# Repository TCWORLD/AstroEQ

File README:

Last Updated: 12/02/2017

Version 7 includes a change to the microstepping mode being used. AstroEQ now has a user selectable stepping modes allowing used of all modes supported by the DRV8825 and A4988 chips. If you have legacy hardware, please read the "Upgrading from 6.x to 7.x firmware" file. The Arduino Mega variant of the design has been adjusted as described in the upgrade file to bring it up to date and as such, it is no longer considered legacy hardware.

A small number of AstroEQ controllers are available to purchase. These can be bought from me on my website (http://www.astroeq.co.uk).

If you have any questions or need support, I have opened an AstroEQ Forum which can be found at http://www.astroeq.co.uk/forum/

The AstroEQ Firmware is currently proving to be very stable. If you do happen across any glitches, let me know as I can usually fix them fairly quickly.

There are two hardware options. Firstly to use an Arduino Mega (Uno is not supported), which requires only two DRV8825 or A4988 driver boards and a couple of capacitors to build.
The second option which is used for purchased controllers is a completely custom hardware which is based around an Atmega162 chip. Although this is not officially supported by the Arduino IDE, I have modified the bootloader to suit.
Schematic and PCB Layout designs are available in this repo for the second option. For the Mega, refer to the PinAssignments.h file for the digital pin numbers to connect the driver boards.

-------------------------------------------------------------------------------------

AstroEQ Arduino code, and Hardware schematics.

AstroEQ was written and designed by Thomas Carpenter.
With thanks Chris over at the EQMOD Yahoo group for help communicating with EQMOD.

AstroEQ is an alternative to the expensive SynScan upgrade. The project acts as a gateway to connect the EQMOD Software (and hence ASCOM planetariums) to a motorised Equatorial mount that lacks Goto functionality.

The EQMOD Project can be found at: http://eq-mod.sourceforge.net/

  Works with EQ3, EQ5, HEQ5, and EQ6 mounts. Along With custom mounts.
 
  Current Config Utility Version: 3.6
  Current Software Verison: 7.5
  Current Hardware Version: 4.6

---------------------------------------------------------------------------------------

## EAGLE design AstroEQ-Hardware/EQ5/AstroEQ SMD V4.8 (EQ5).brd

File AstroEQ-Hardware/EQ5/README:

This is an experimental design I am using for my mount.

It is designed to fit within the shell of a Skywatcher EQ5, though takes a bit of work to install it.

I don't recommend using this design. It is provided as-is without any support.

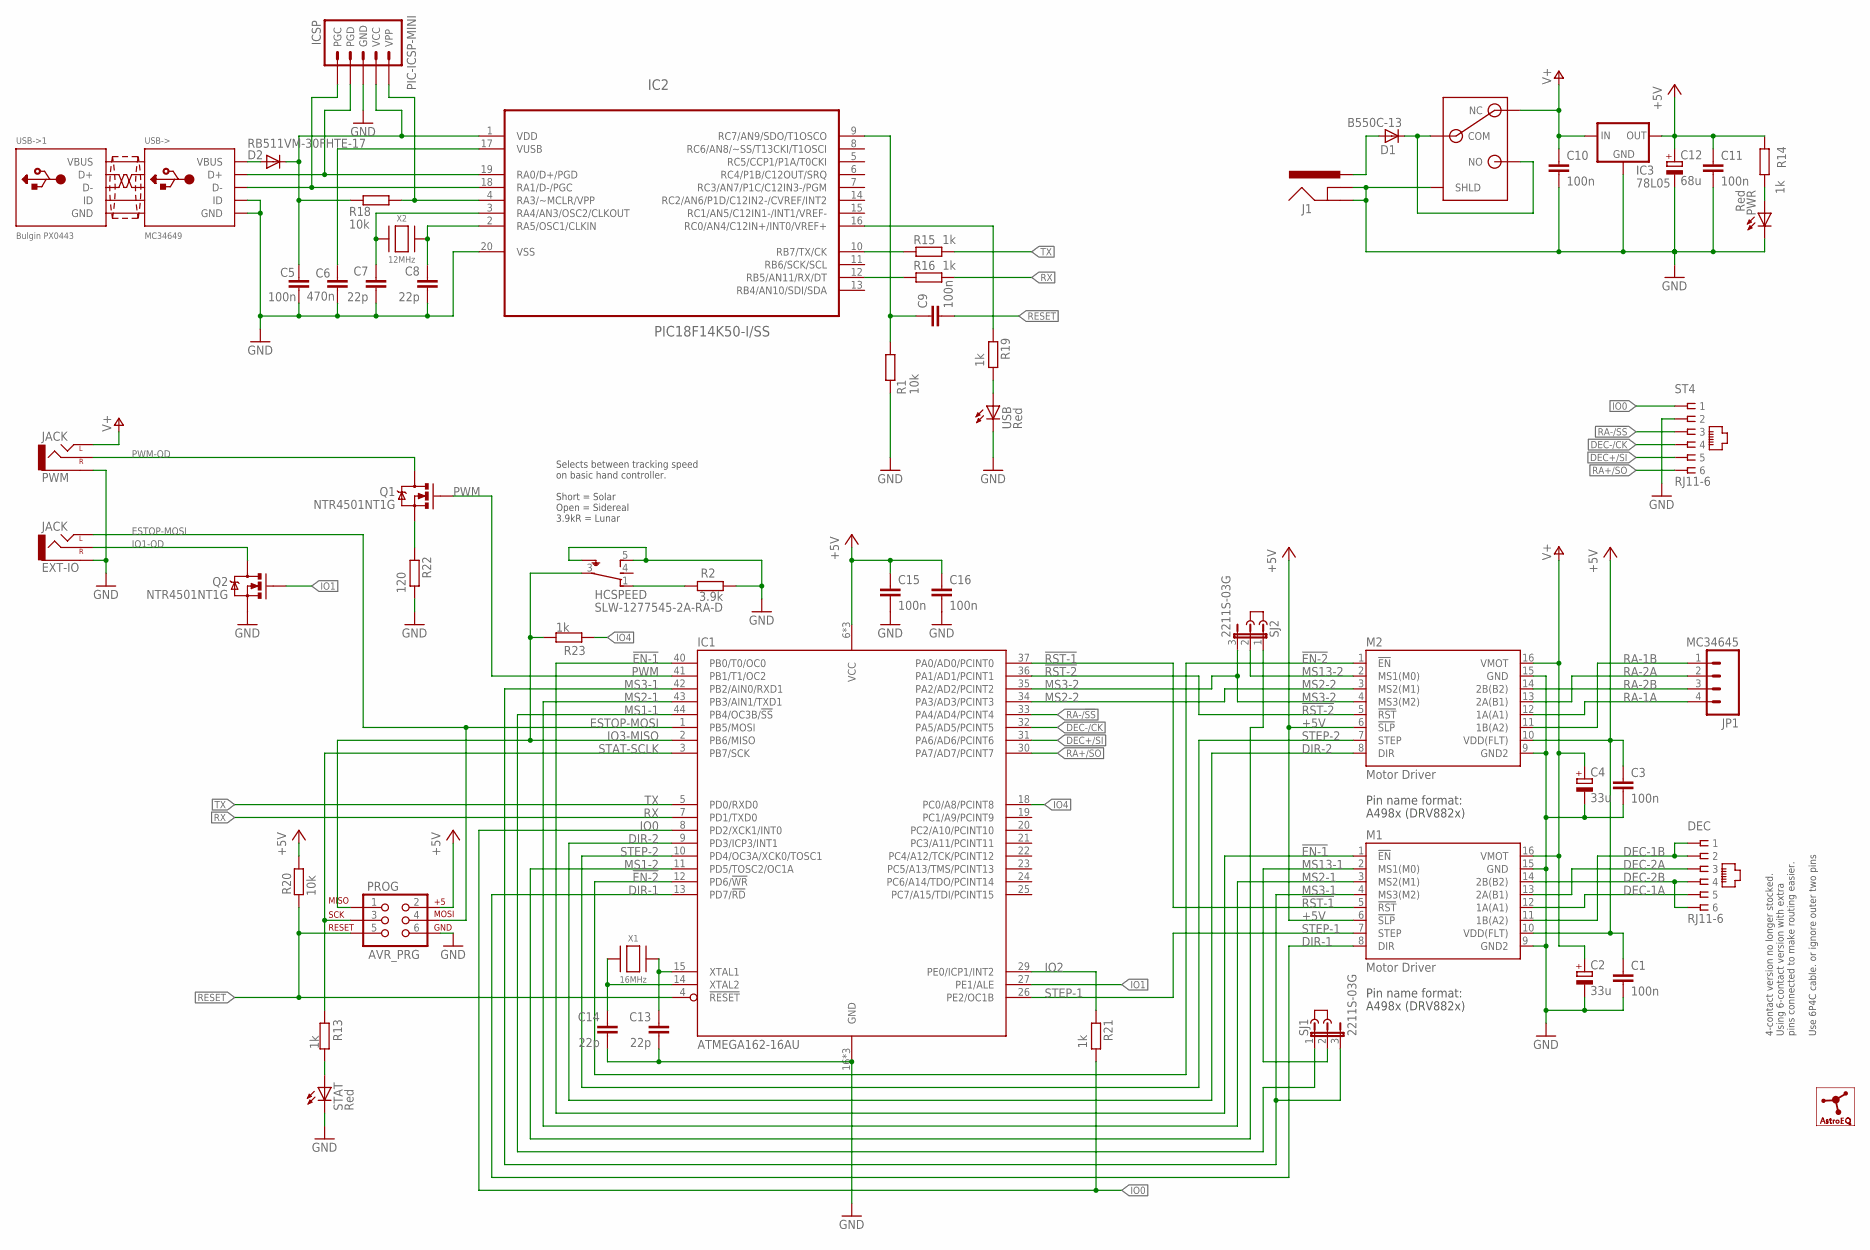
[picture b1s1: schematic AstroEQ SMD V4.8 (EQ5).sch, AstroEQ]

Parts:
C1, C3, C5, C9, C10, C11, C15, C16: 100n; C0603; MPN MC0603F104Z250CT
C2, C4: 33u; SMC_C; MPN T491C336K025AT
C6: 470n; C0603; MPN MC0603F474Z160CT
C7, C8, C13, C14: 22p; C0603; MPN MC0603N220J500CT
C12: 68u; SMC_C; MPN TPSC686K016R0125
D1: B550C-13; SMC; MPN B550C-13-F
D2: RB511VM-30FHTE-17; SOD-323; MPN RB511VM-30FHTE-17
DEC: RJ11-6; RJ11-NO_SHIELD; MPN 95503-2661
EXT-IO: JACK; AUDIO-JACK-3.5MM-VERT
HCSPEED: SLW-1277545-2A-RA-D; SLW-127
IC1: ATMEGA162-16AU; TQFP44; MPN ATMEGA162-16AU
IC2: PIC18F14K50-I/SS; SS20
IC3: 78L05; SOT23; MPN TS78L05CX RFG
ICSP: PIC-ICSP-MINI
J1: POWER_JACKPANEL; POWER_JACK_PANEL; MPN PCL712AS
J2, J3: DNI; JUMP; MPN 969102-0000-DA
JP1: MC34645; MOLEX-1X4; MPN MC34645
LOGO1: ASTROEQ5MM; ASTROEQ-SMALL
M1, M2: Motor Driver; DIP16-W; MPN CES-116-01-T-S
PROG: AVR_PRG; 2X3; MPN 826632-3
PWM: JACK; AUDIO-JACK-3.5MM-VERT
PWR: Red; LED3MM; MPN L-424HDT
PWR-SW: SWITCH; SPST; MPN AE101J1V3B004
Q1, Q2: NTR4501NT1G; SOT23-3; MPN NTR4501NT1G
R1, R18, R20: 10k; R0603; MPN MCWR06X1002FTL
R2: 3.9k; R0603; MPN MCWR06X1001FTL
R13, R14, R15, R16, R19, R21, R23: 1k; R0603; MPN MCWR06X1001FTL
R22: 120; R0805; MPN MCWR08X1200FTL
SJ1, SJ2: 2211S-03G; JP2; MPN 2211S-03G
ST4: RJ11-6; RJ11-NO_SHIELD; MPN 95503-2661
STAT: Red; LED3MM; MPN L-424HDT
USB: Red; LED3MM; MPN L-424HDT
USB->: MC34649; 22-23-2051; MPN MC34647
X1: 16MHz; NX5032; MPN 7A-16.000MAAJ-T
X2: 12MHz; NX5032; MPN 7A-12.000MAAJ-T

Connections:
!EN-1: IC1.40 (PB0/T0/OC0), M1.1 (!EN)
!EN-2: IC1.12 (PD6/!WR), M2.1 (!EN)
!RST-1: IC1.37 (PA0/AD0/PCINT0), M1.5 (!RST)
!RST-2: IC1.36 (PA1/AD1/PCINT1), M2.5 (!RST)
+5V: C1.1, C3.1, C11.1, C12.+, C15.1, C16.1, IC1.6 (VCC), IC1.17 (VCC), IC1.38 (VCC), IC3.1 (OUT), M1.6 (!SLP), M1.10 (VDD(FLT)), M2.6 (!SLP), M2.10 (VDD(FLT)), PROG.2, R14.1, R20.2
AVROSC1: C13.1, IC1.15 (XTAL1), X1.1
AVROSC2: C14.1, IC1.14 (XTAL2), X1.2
DEC+/SI: IC1.31 (PA6/AD6/PCINT6), ST4.5
DEC-1A: DEC.5, M1.12 (1A(A1))
DEC-1B: DEC.1, DEC.2, M1.11 (1B(A2))
DEC-2A: DEC.3, M1.13 (2A(B1))
DEC-2B: DEC.4, DEC.6, M1.14 (2B(B2))
DEC-/CK: IC1.32 (PA5/AD5/PCINT5), ST4.4
DIR-1: IC1.13 (PD7/!RD), M1.8 (DIR)
DIR-2: IC1.9 (PD3/ICP3/INT1), M2.8 (DIR)
DTR: C9.1, IC2.9 (RC7/AN9/SDO/T1OSCO), R1.1
D_N: IC2.18 (RA1/D-/PGC), ICSP.5 (PGC), USB->.2 (D-)
D_P: IC2.19 (RA0/D+/PGD), ICSP.4 (PGD), USB->.3 (D+)
ESTOP-MOSI: EXT-IO.2 (LEFT), IC1.1 (PB5/MOSI), PROG.4
GND: C1.2, C2.-, C3.2, C4.-, C5.2, C6.1, C7.2, C8.2, C10.2, C11.2, C12.-, C13.2, C14.2, C15.2, C16.2, EXT-IO.1 (SLEEVE), HCSPEED.5 (O), HCSPEED.S1 (SH), HCSPEED.S2 (SH), IC1.16 (GND), IC1.28 (GND), IC1.39 (GND), IC2.20 (VSS), IC3.3 (GND), ICSP.3 (GND), J1.SHUNT (GNDBREAK), J1.SLEEVE (GND), M1.9 (GND2), M1.15 (GND), M2.9 (GND2), M2.15 (GND), PROG.6, PWM.1 (SLEEVE), PWR.K (C), PWR-SW.S1 (SHLD), PWR-SW.S2 (SHLD), PWR-SW.S3 (SHLD), PWR-SW.S4 (SHLD), Q2.2 (S), R1.2, R2.2, R22.1, ST4.2, STAT.K (C), USB.K (C), USB->.4 (GND), USB->.5 (ID)
IO0: IC1.8 (PD2/XCK1/INT0), R21.1, ST4.1
IO1: IC1.27 (PE1/ALE), Q2.1 (G)
IO1-OD: EXT-IO.3 (RIGHT), Q2.3 (D)
IO2: IC1.29 (PE0/ICP1/INT2), R21.2
IO3-MISO: HCSPEED.3, IC1.2 (PB6/MISO), PROG.1, R23.2
IO4: IC1.18 (PC0/A8/PCINT8), R23.1
MCLR: IC2.4 (RA3/~MCLR/VPP), ICSP.1 (VPP), R18.1
MS1-1: IC1.44 (PB4/OC3B/!SS), SJ1.1
MS1-2: IC1.11 (PD5/TOSC2/OC1A), SJ2.1
MS2-1: IC1.43 (PB3/AIN1/TXD1), M1.3 (MS2(M1))
MS2-2: IC1.34 (PA3/AD3/PCINT3), M2.3 (MS2(M1))
MS3-1: IC1.42 (PB2/AIN0/RXD1), M1.4 (MS3(M2)), SJ1.3
MS3-2: IC1.35 (PA2/AD2/PCINT2), M2.4 (MS3(M2)), SJ2.3
MS13-1: M1.2 (MS1(M0)), SJ1.2
MS13-2: M2.2 (MS1(M0)), SJ2.2
unnamed: HCSPEED.1 (S), R2.1
PWM: IC1.41 (PB1/T1/OC2), Q1.1 (G)
PWM-OD: PWM.3 (RIGHT), Q1.3 (D)
PWM-RES: Q1.2 (S), R22.2
PWRLED: PWR.A, R14.2
RA+/SO: IC1.30 (PA7/AD7/PCINT7), ST4.6
RA-1A: JP1.4, M2.12 (1A(A1))
RA-1B: JP1.1, M2.11 (1B(A2))
RA-2A: JP1.2, M2.13 (2A(B1))
RA-2B: JP1.3, M2.14 (2B(B2))
RA-/!SS: IC1.33 (PA4/AD4/PCINT4), ST4.3
RESET: C9.2, IC1.4 (!RESET), PROG.5, R20.1
RX: IC1.7 (PD1/TXD0), R16.1
RX(USB): IC2.12 (RB5/AN11/RX/DT), R16.2
STAT-SCLK: IC1.3 (PB7/SCK), PROG.3, R13.1
STATLED: R13.2, STAT.A
STEP-1: IC1.26 (PE2/OC1B), M1.7 (STEP)
STEP-2: IC1.10 (PD4/OC3A/XCK0/TOSC1), M2.7 (STEP)
SWITCH: D1.C, PWR-SW.COM, PWR-SW.NO
TX: IC1.5 (PD0/RXD0), R15.1
TX(USB): IC2.10 (RB7/TX/CK), R15.2
USBLED: R19.1, USB.A
USBOSC1: C8.1, IC2.2 (RA5/OSC1/CLKIN), X2.2
USBOSC2: C7.1, IC2.3 (RA4/AN3/OSC2/CLKOUT), X2.1
USBSTAT: IC2.16 (RC0/AN4/C12IN+/INT0/VREF+), R19.2
V+: C2.+, C4.+, C10.1, IC3.2 (IN), M1.16 (VMOT), M2.16 (VMOT), PWM.2 (LEFT), PWR-SW.NC
VBUS: D2.2 (A), USB->.1 (VBUS)
VIN: D1.A, J1.CENTRE (PWR)
VPIC: C5.1, D2.1 (C), IC2.1 (VDD), ICSP.2 (VCC), R18.2
VUSB: C6.2, IC2.17 (VUSB)

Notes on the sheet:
4-contact version no longer stocked. Using 6-contact version with extra pins connected to make routing easier. Use 6P4C cable. or ignore outer two pins
Selects between tracking speed on basic hand controller. Short = Solar Open = Sidereal 3.9kR = Lunar

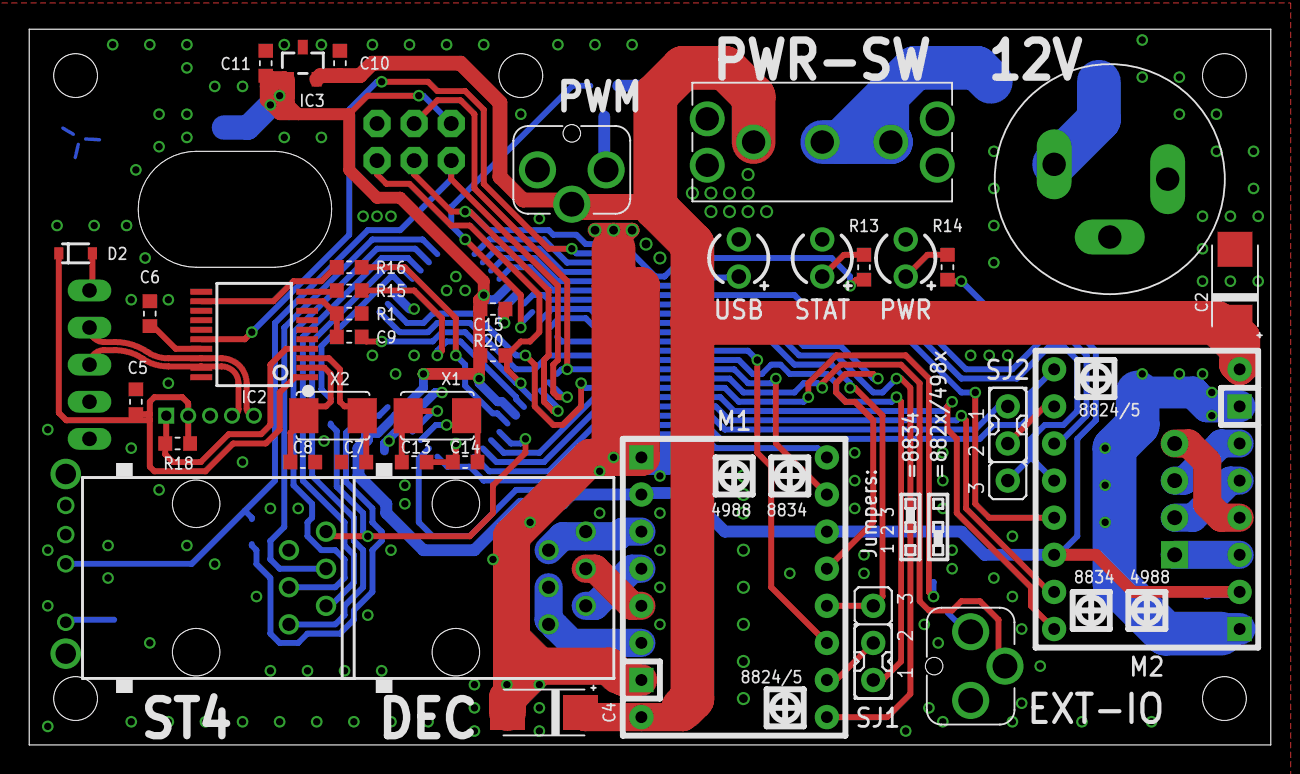
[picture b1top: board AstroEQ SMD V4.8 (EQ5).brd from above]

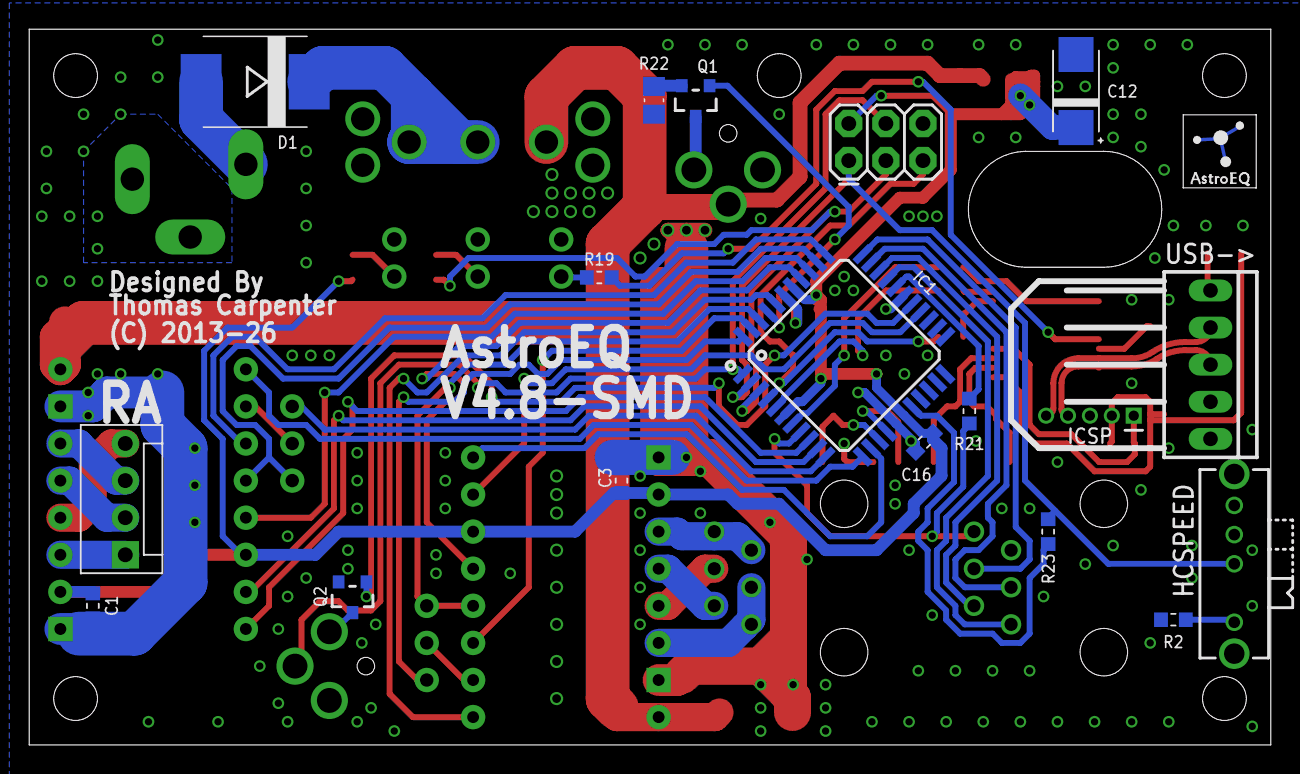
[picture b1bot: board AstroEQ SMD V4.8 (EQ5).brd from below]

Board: 2 copper layers, 85.0 x 49.0 mm, 58 parts (19 on the bottom side), 65 nets.

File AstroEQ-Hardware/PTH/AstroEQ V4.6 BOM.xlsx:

Qty | Parts | Value | Description | Manufacturer | Part Number | Farnell Code
2 | SJ1, SJ2 | - | Solder Jumper - See PCB for details | - | - | -
7 | C1, C3, C5, C9, C10, C11, C15 | 100nF | 100nF Ceramic Capacitor, 50V, 2.54mm pitch | MULTICOMP | MCRR25104X7RK0050 | 1216438
3 | C2, C4, C12 | 100uF | 100uF Alu Electrolytic Capacitor, 25V, Dia 6.3mm | MULTICOMP | MCGPR25V107M6.3X11 | 9451188
4 | C7, C8, C13, C14 | 22pF | 22pF Ceramic Capacitor, 2.54mm pitch | AVX | SR151A220JAR | 1100369
1 | D1 | MBR1060 | TO-220 Schottky Diode, 10A | MULTICOMP | MBR1060 | 1625119
1 | ST4 | RJ11-6 | RJ11 JACK, 6/6 LOW PROFILE | MOLEX | 95501-2661 | 1536490
2 | DEC, RA | RJ11-4 | RJ11 JACK, 6/4 LOW PROFILE | MOLEX | 95501-2641 | 1560166
1 | HAMMOND-1593N | HAMMOND-1593N | CASE, ABS, HANDHELD, BLACK, 111X75X25MM | HAMMOND | 1593NBK | 9287566
1 | IC1 | ATMEGA162-16PU | IC, ATMEGA162-16PU, DIP40 | ATMEL | ATMEGA162-16PU | 9171169
1 | IC1 | DIP40 Socket | 40Way DIP IC Socket, 0.3" Pitch | MULTICOMP | 2227-20-03-07 | 4285608
1 | IC2 | PIC18F14K50-I/P | IC, PIC18F14K50-I/P, PDIP20 | MICROCHIP | PIC18F14K50-I/P | 1648501
1 | IC2 | DIP20 Socket | 40Way DIP IC Socket, 0.6" Pitch | MULTICOMP | 2227-40-06-05 | 4285669
1 | IC3 | 78L05 | 5V 100mA Voltage Regulator, TO-92 | FAIRCHILD SEMICONDUCTOR | LM78L05ACZX | 1467367
1 | J1 | MJ-179PH | DC Barrel Jack Socket, PCB Mount | MULTICOMP | MJ-179PH | 1737246
2 | M1, M2 | Motor Driver Socket | RECEPTACLE, 2.54MM, SINGLE, 16WAY | SAMTEC | CES-116-01-T-S | 1667522
1 | PROG | 2x3 Header | 2ROW, 6WAY, 2.54mm Pitch Header | TE CONNECTIVITY / AMP | 826632-3 | 3418492
6 | R13, R14, R15, R16, R19, R21 | 1kR | 1k Resistor, 1/4W, 5% | MULTICOMP | MF12 1K | 9342400
1 | USB-> | Mini USB Connector | MINI USB RECEPTACLE, THT, R/A | MOLEX | 565790519 | 1125347
1 | X2 | 12MHz XTAL | XTAL, 12.000MHZ, 18PF, HC-49S | TXC | 9B-12.000MAAJ-B | 1842203
3 | R1, R18, R20 | 10kR | 10k Resistor, 1/4W, 5% | MULTICOMP | MF12 10K | 9342419
3 | PWR, STAT, USB | 3mm LED Red | Flat Top Red LED, 3mm | KINGBRIGHT | L-424HDT | 1142499
1 | X1 | 16MHz XTAL | XTAL, 16.000MHZ, 18PF, HC-49S | TXC | 9B-16.000MEEJ-B | 1842217
1 | D2 | 1N4148 | DIODE, 100V,150MA, DO-35 | MULTICOMP | 1N4148 | 9565124
1 | C6 | 470nF | 470nF Ceramic Capacitor, 50V, 2.54mm pitch | KEMET | C320C474M5U5TA | 1457660
1 | R22 | 120R | 120R Resistor, 1/4W, 5% | MULTICOMP | MF12 120R | 9342516
1 | Q1 | BS270 | MOSFET TRANSISTOR, N CHANNEL, BS270 | FAIRCHILD SEMICONDUCTOR | BS270 | 1017689
1 | PWM | 3.5mm JACK | PHONE AUDIO CONNECTOR, JACK, 3.5MM | CLIFF ELECTRONIC COMPONENETS | FC68131 | 2518188
1 Pack | - | Mounting PCB to Case | WASHER, FLAT, NYLON, M2.5, PK50 | DURATOOL | 110764 | 7047472
1 Pack | - | Mounting PCB to Case | SCREW, POZI PAN, STEEL, BZP, M2.5X6 | TR FASTENINGS | M2.56 PRSTTTZ100 | 1420119

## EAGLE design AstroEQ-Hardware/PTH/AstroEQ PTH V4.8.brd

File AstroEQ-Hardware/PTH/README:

This folder contains designs used in purchased AstroEQ controllers and PCBs.

Currently V4.6 is the bare PCB version that I sell through the AstroEQ website. It is an easy to solder through-hole board. The Gerber files, Schematic and BOM, as well as the Eagle design files are all available in this folder.

V4.7 is a new part-SMD design that I will be using for the next run of controllers. I have made this switch to allow for machine assembly of the design. I would not recommend building this board yourself as it is functionally identical to the V4.6 board but will not be easy to assemble!

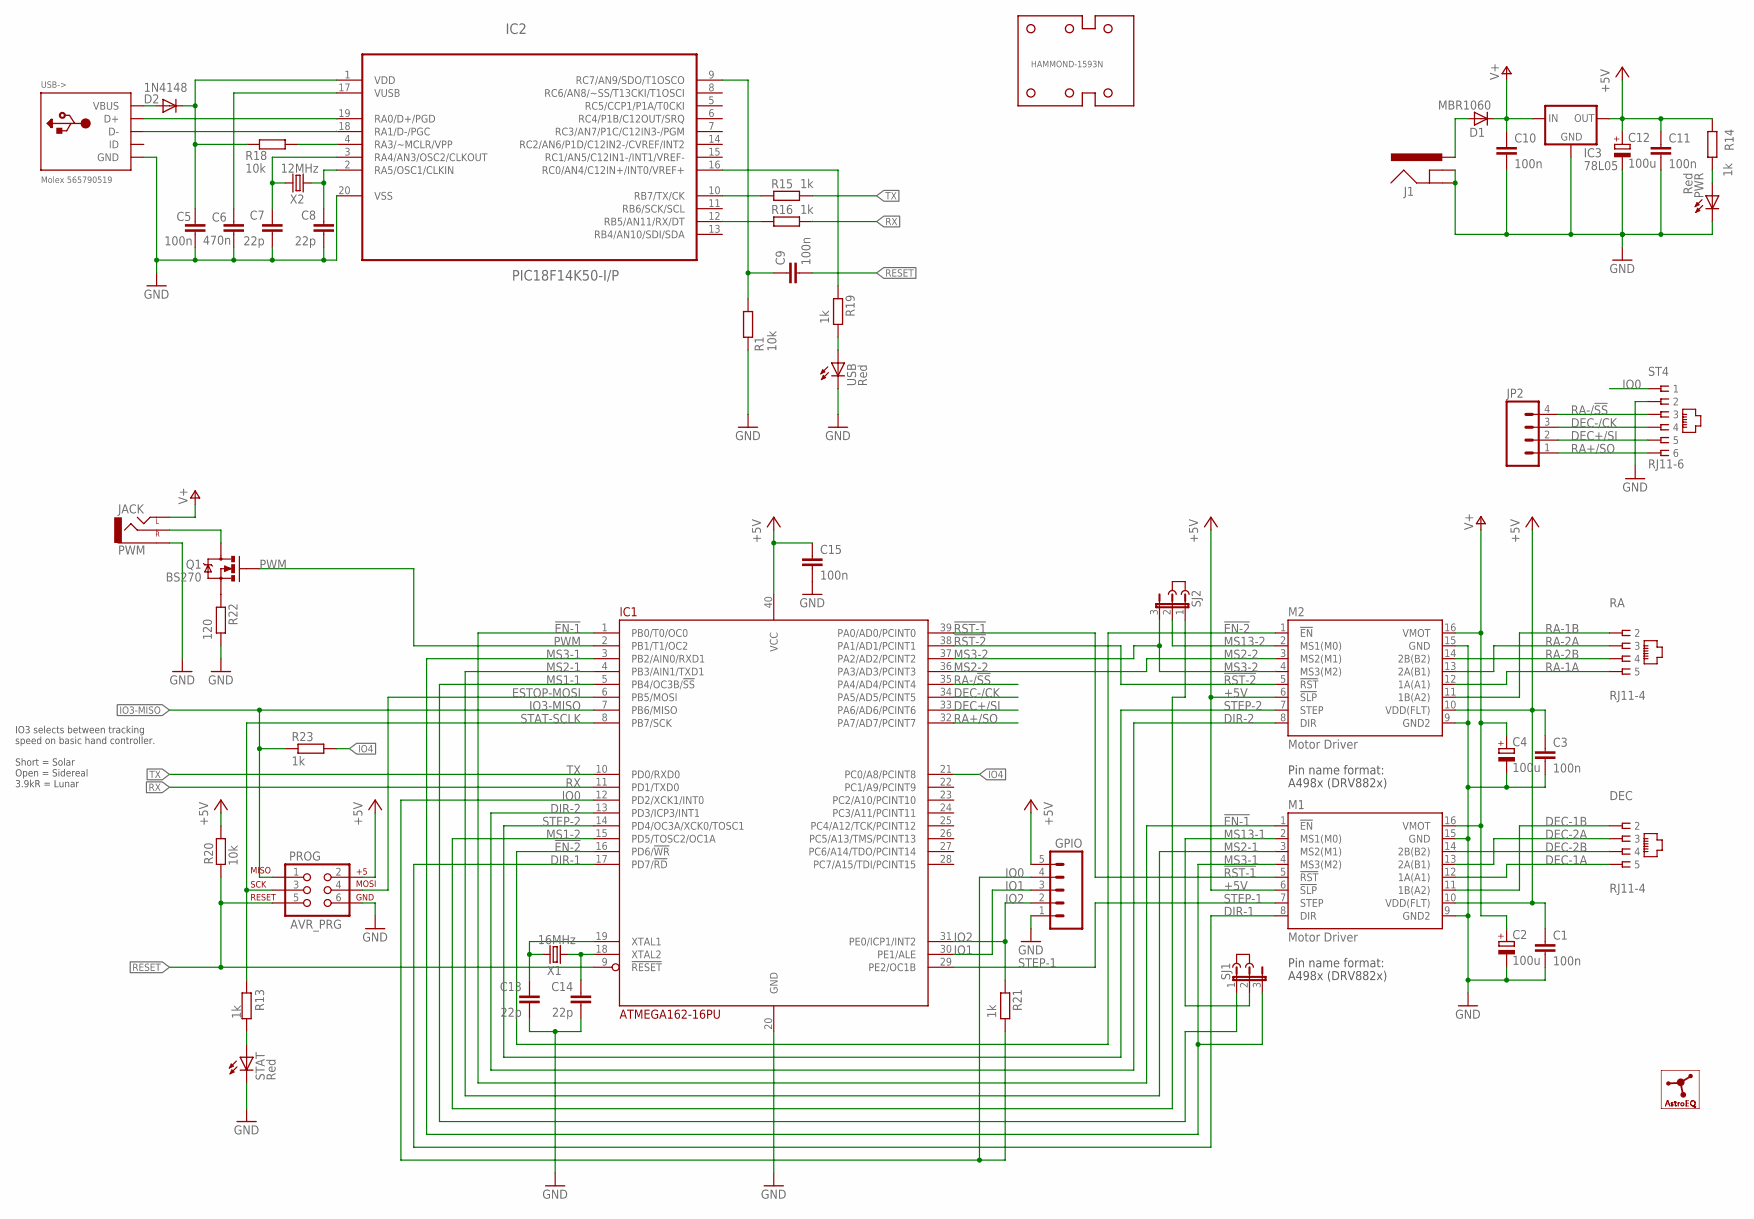
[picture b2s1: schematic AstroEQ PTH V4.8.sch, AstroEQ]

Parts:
C1, C3, C5, C9, C10, C11, C15: 100n; C025-024X044; MPN SR205C104KAR
C2, C4, C12: 100u; E2,5-7; MPN MCGPR25V107M6.3X11
C6: 470n; C025-024X044; MPN C320C474M5U5TA
C7, C8, C13, C14: 22p; C025-024X044; MPN SR151A220JAR
D1: MBR1060; C221B1A; MPN MBR1060
D2: 1N4148; DIODE-1N4148; MPN 1N4148.
DEC: RJ11-4; RJ11-NO_SHIELD-4; MPN 95501-2641
GPIO: M05PTH; 1X05; MPN SSF211X050
HAMMOND-1593N: HAMMOND-1593N-4HOLE; HAMMOND-1593N4HOLES; MPN 1593NBK
IC1: ATMEGA162-16PU; DIL40; MPN ATMEGA162-16PU
IC2: PIC18F14K50-I/P; DIL20
IC3: 78L05; TO-92; MPN LM78L05ACZX
J1: POWER_JACKPTH; POWER_JACK_PTH; MPN MJ-179PH
J2, J3: JUMPER; JUMP
JP2: M04PTH; 1X04
LOGO1: ASTROEQ5MM; ASTROEQ-SMALL
M1, M2: Motor Driver; DIP16-W; MPN CES-116-01-T-S
PROG: AVR_PRG; 2X3; MPN 826632-3
PWM: JACK; AUDIO-JACK; MPN FC68131
PWR: Red; LED3MM; MPN L-424HDT
Q1: BS270; TO-92; MPN BS270
R1, R18, R20: 10k; 0204/7; MPN MF12 10K
R13, R14, R15, R16, R19, R21: 1k; 0204/7; MPN MF12 1K
R22: 120; 0204/7; MPN MF12 120R
R23: 1k; 0207/10; MPN MF12 1K
RA: RJ11-4; RJ11-NO_SHIELD-4; MPN 95501-2641
SJ1, SJ2: JP2EL; JP2L
ST4: RJ11-6; RJ11-NO_SHIELD; MPN 95501-2661
STAT: Red; LED3MM; MPN L-424HDT
USB: Red; LED3MM; MPN L-424HDT
USB->: Molex 565790519; USB-MINIB-THM-MOLEX; MPN 565790519
X1: 16MHz; HC49US; MPN 9B-16.000MEEJ-B
X2: 12MHz; HC49US; MPN 9B-12.000MAAJ-B

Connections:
!EN-1: IC1.1 (PB0/T0/OC0), M1.1 (!EN)
!EN-2: IC1.16 (PD6/!WR), M2.1 (!EN)
!RST-1: IC1.39 (PA0/AD0/PCINT0), M1.5 (!RST)
!RST-2: IC1.38 (PA1/AD1/PCINT1), M2.5 (!RST)
+5V: C1.1, C3.1, C11.1, C12.+, C15.1, GPIO.5, IC1.40 (VCC), IC3.1 (OUT), M1.6 (!SLP), M1.10 (VDD(FLT)), M2.6 (!SLP), M2.10 (VDD(FLT)), PROG.2, R14.1, R20.2
AVROSC1: C13.1, IC1.19 (XTAL1), X1.2
AVROSC2: C14.1, IC1.18 (XTAL2), X1.1
D+: IC2.19 (RA0/D+/PGD), USB->.D+
D-: IC2.18 (RA1/D-/PGC), USB->.D-
DEC+/SI: IC1.33 (PA6/AD6/PCINT6), JP2.2, ST4.5
DEC-1A: DEC.5, M1.12 (1A(A1))
DEC-1B: DEC.2, M1.11 (1B(A2))
DEC-2A: DEC.3, M1.13 (2A(B1))
DEC-2B: DEC.4, M1.14 (2B(B2))
DEC-/CK: IC1.34 (PA5/AD5/PCINT5), JP2.3, ST4.4
DIR-1: IC1.17 (PD7/!RD), M1.8 (DIR)
DIR-2: IC1.13 (PD3/ICP3/INT1), M2.8 (DIR)
DTR: C9.1, IC2.9 (RC7/AN9/SDO/T1OSCO), R1.1
ESTOP-MOSI: IC1.6 (PB5/MOSI), PROG.4
GND: C1.2, C2.-, C3.2, C4.-, C5.2, C6.1, C7.2, C8.2, C10.2, C11.2, C12.-, C13.2, C14.2, C15.2, GPIO.1, IC1.20 (GND), IC2.20 (VSS), IC3.2 (GND), J1.GND, J1.GNDBREAK, M1.9 (GND2), M1.15 (GND), M2.9 (GND2), M2.15 (GND), PROG.6, PWM.SLEEVE, PWR.K (C), R1.2, R22.1, ST4.2, STAT.K (C), USB.K (C), USB->.GND, USB->.GND1 (GND), USB->.GND4 (GND)
IO0: GPIO.4, IC1.12 (PD2/XCK1/INT0), R21.1, ST4.1
IO1: GPIO.3, IC1.30 (PE1/ALE)
IO2: GPIO.2, IC1.31 (PE0/ICP1/INT2), R21.2
IO3-MISO: IC1.7 (PB6/MISO), PROG.1, R23.1
IO4: IC1.21 (PC0/A8/PCINT8), R23.2
MCLR: IC2.4 (RA3/~MCLR/VPP), R18.1
MS1-1: IC1.5 (PB4/OC3B/!SS), SJ1.1
MS1-2: IC1.15 (PD5/TOSC2/OC1A), SJ2.1
MS2-1: IC1.4 (PB3/AIN1/TXD1), M1.3 (MS2(M1))
MS2-2: IC1.36 (PA3/AD3/PCINT3), M2.3 (MS2(M1))
MS3-1: IC1.3 (PB2/AIN0/RXD1), M1.4 (MS3(M2)), SJ1.3
MS3-2: IC1.37 (PA2/AD2/PCINT2), M2.4 (MS3(M2)), SJ2.3
MS13-1: M1.2 (MS1(M0)), SJ1.2
MS13-2: M2.2 (MS1(M0)), SJ2.2
PWM: IC1.2 (PB1/T1/OC2), Q1.2 (G)
PWM-ILIM: Q1.3 (S), R22.2
PWM-OUT: PWM.RING (RIGHT), Q1.1 (D)
PWRLED: PWR.A, R14.2
RA+/SO: IC1.32 (PA7/AD7/PCINT7), JP2.1, ST4.6
RA-1A: M2.12 (1A(A1)), RA.5
RA-1B: M2.11 (1B(A2)), RA.2
RA-2A: M2.13 (2A(B1)), RA.3
RA-2B: M2.14 (2B(B2)), RA.4
RA-/!SS: IC1.35 (PA4/AD4/PCINT4), JP2.4, ST4.3
RESET: C9.2, IC1.9 (!RESET), PROG.5, R20.1
RX: IC1.11 (PD1/TXD0), R16.1
RX(USB): IC2.12 (RB5/AN11/RX/DT), R16.2
STAT-SCLK: IC1.8 (PB7/SCK), PROG.3, R13.1
STATLED: R13.2, STAT.A
STEP-1: IC1.29 (PE2/OC1B), M1.7 (STEP)
STEP-2: IC1.14 (PD4/OC3A/XCK0/TOSC1), M2.7 (STEP)
TX: IC1.10 (PD0/RXD0), R15.1
TX(USB): IC2.10 (RB7/TX/CK), R15.2
USBLED: R19.1, USB.A
USBOSC1: C8.1, IC2.2 (RA5/OSC1/CLKIN), X2.1
USBOSC2: C7.1, IC2.3 (RA4/AN3/OSC2/CLKOUT), X2.2
USBSTAT: IC2.16 (RC0/AN4/C12IN+/INT0/VREF+), R19.2
V+: C2.+, C4.+, C10.1, D1.C, IC3.3 (IN), M1.16 (VMOT), M2.16 (VMOT), PWM.TIP (LEFT)
VBUS: D2.A, USB->.VBUS
VIN: D1.A, J1.PWR
VPIC: C5.1, D2.C, IC2.1 (VDD), R18.2
VUSB: C6.2, IC2.17 (VUSB)

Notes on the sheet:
IO3 selects between tracking speed on basic hand controller. Short = Solar Open = Sidereal 3.9kR = Lunar

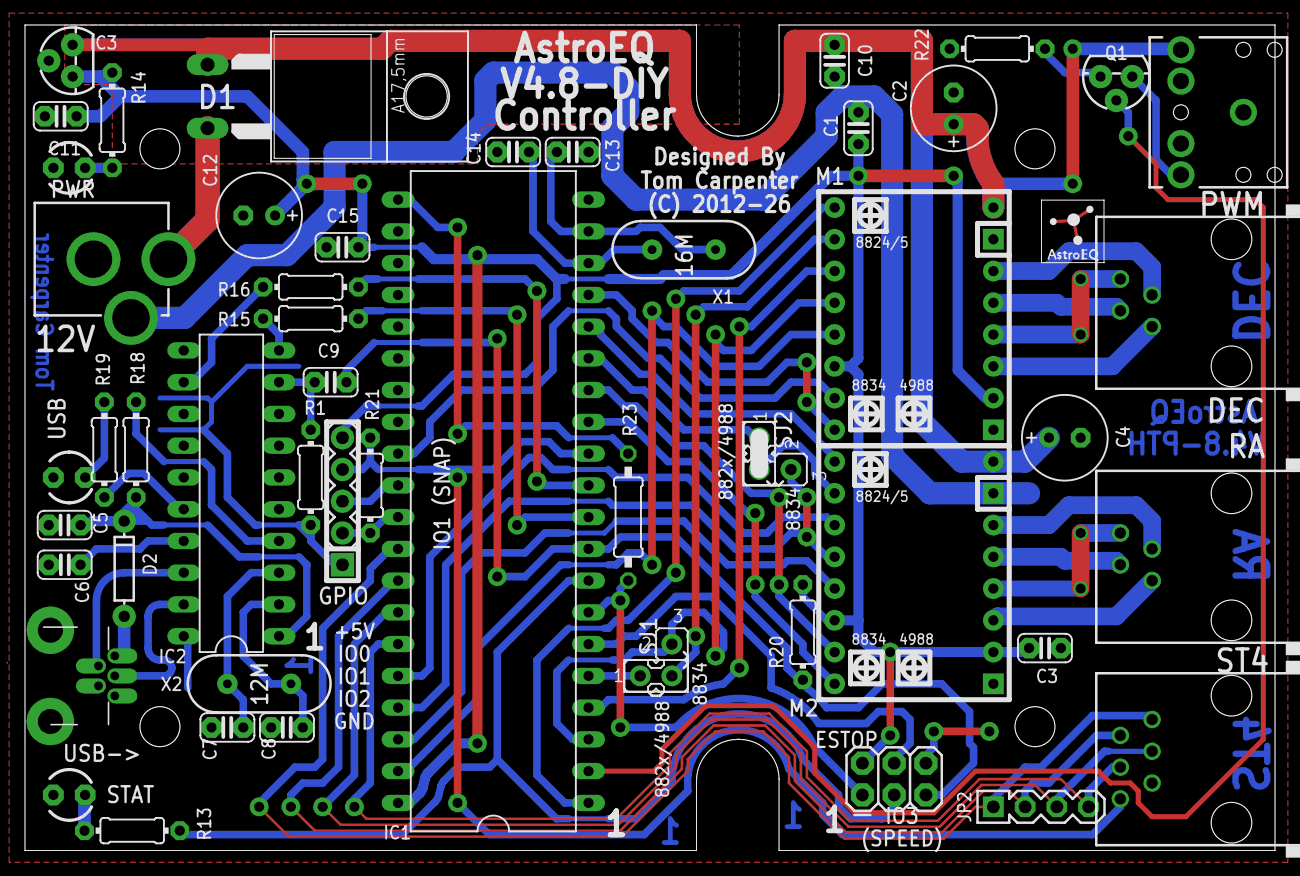
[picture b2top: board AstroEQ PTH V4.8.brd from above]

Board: 2 copper layers, 100.0 x 66.0 mm, 54 parts (0 on the bottom side), 62 nets.

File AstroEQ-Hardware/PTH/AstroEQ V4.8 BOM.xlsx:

Qty | Parts | Value | Description | Manufacturer | Part Number | Farnell Code
2 | SJ1, SJ2 | - | Solder Jumper - See PCB for details | - | - | -
7 | C1, C3, C5, C9, C10, C11, C15 | 100nF | 100nF Ceramic Capacitor, 50V, 2.54mm pitch | MULTICOMP | MCRR25104X7RK0050 | 1216438
3 | C2, C4, C12 | 100uF | 100uF Alu Electrolytic Capacitor, 25V, Dia 6.3mm | MULTICOMP | MCGPR25V107M6.3X11 | 9451188
4 | C7, C8, C13, C14 | 22pF | 22pF Ceramic Capacitor, 2.54mm pitch | AVX | SR151A220JAR | 1100369
1 | D1 | MBR1060 | TO-220 Schottky Diode, 10A | MULTICOMP | MBR1060 | 1625119
1 | ST4 | RJ11-6 | RJ11 JACK, 6/6 LOW PROFILE | MOLEX | 95501-2661 | 1536490
2 | DEC, RA | RJ11-4 | RJ11 JACK, 6/4 LOW PROFILE | MOLEX | 95501-2641 | 1560166
1 | HAMMOND-1593N | HAMMOND-1593N | CASE, ABS, HANDHELD, BLACK, 111X75X25MM | HAMMOND | 1593NBK | 9287566
1 | IC1 | ATMEGA162-16PU | IC, ATMEGA162-16PU, DIP40 | ATMEL | ATMEGA162-16PU | 9171169
1 | IC1 | DIP40 Socket | 40Way DIP IC Socket, 0.3" Pitch | MULTICOMP | 2227-20-03-07 | 4285608
1 | IC2 | PIC18F14K50-I/P | IC, PIC18F14K50-I/P, PDIP20 | MICROCHIP | PIC18F14K50-I/P | 1648501
1 | IC2 | DIP20 Socket | 40Way DIP IC Socket, 0.6" Pitch | MULTICOMP | 2227-40-06-05 | 4285669
1 | IC3 | 78L05 | 5V 100mA Voltage Regulator, TO-92 | FAIRCHILD SEMICONDUCTOR | LM78L05ACZX | 1467367
1 | J1 | MJ-179PH | DC Barrel Jack Socket, PCB Mount | MULTICOMP | MJ-179PH | 1737246
2 | M1, M2 | Motor Driver Socket | RECEPTACLE, 2.54MM, SINGLE, 16WAY | SAMTEC | CES-116-01-T-S | 1667522
1 | PROG | 2x3 Header | 2ROW, 6WAY, 2.54mm Pitch Header | TE CONNECTIVITY / AMP | 826632-3 | 3418492
7 | R13, R14, R15, R16, R19, R21, R23 | 1kR | 1k Resistor, 1/4W, 5% | MULTICOMP | MF12 1K | 9342400
1 | USB-> | Mini USB Connector | MINI USB RECEPTACLE, THT, R/A | MOLEX | 565790519 | 1125347
1 | X2 | 12MHz XTAL | XTAL, 12.000MHZ, 18PF, HC-49S | TXC | 9B-12.000MAAJ-B | 1842203
3 | R1, R18, R20 | 10kR | 10k Resistor, 1/4W, 5% | MULTICOMP | MF12 10K | 9342419
3 | PWR, STAT, USB | 3mm LED Red | Flat Top Red LED, 3mm | KINGBRIGHT | L-424HDT | 1142499
1 | X1 | 16MHz XTAL | XTAL, 16.000MHZ, 18PF, HC-49S | TXC | 9B-16.000MEEJ-B | 1842217
1 | D2 | 1N4148 | DIODE, 100V,150MA, DO-35 | MULTICOMP | 1N4148 | 9565124
1 | C6 | 470nF | 470nF Ceramic Capacitor, 50V, 2.54mm pitch | KEMET | C320C474M5U5TA | 1457660
1 | R22 | 120R | 120R Resistor, 1/4W, 5% | MULTICOMP | MF12 120R | 9342516
1 | Q1 | BS270 | MOSFET TRANSISTOR, N CHANNEL, BS270 | FAIRCHILD SEMICONDUCTOR | BS270 | 1017689
1 | PWM | 3.5mm JACK | PHONE AUDIO CONNECTOR, JACK, 3.5MM | CLIFF ELECTRONIC COMPONENETS | FC68131 | 2518188
1 Pack | - | Mounting PCB to Case | WASHER, FLAT, NYLON, M2.5, PK50 | DURATOOL | 110764 | 7047472
1 Pack | - | Mounting PCB to Case | SCREW, POZI PAN, STEEL, BZP, M2.5X6 | TR FASTENINGS | M2.56 PRSTTTZ100 | 1420119

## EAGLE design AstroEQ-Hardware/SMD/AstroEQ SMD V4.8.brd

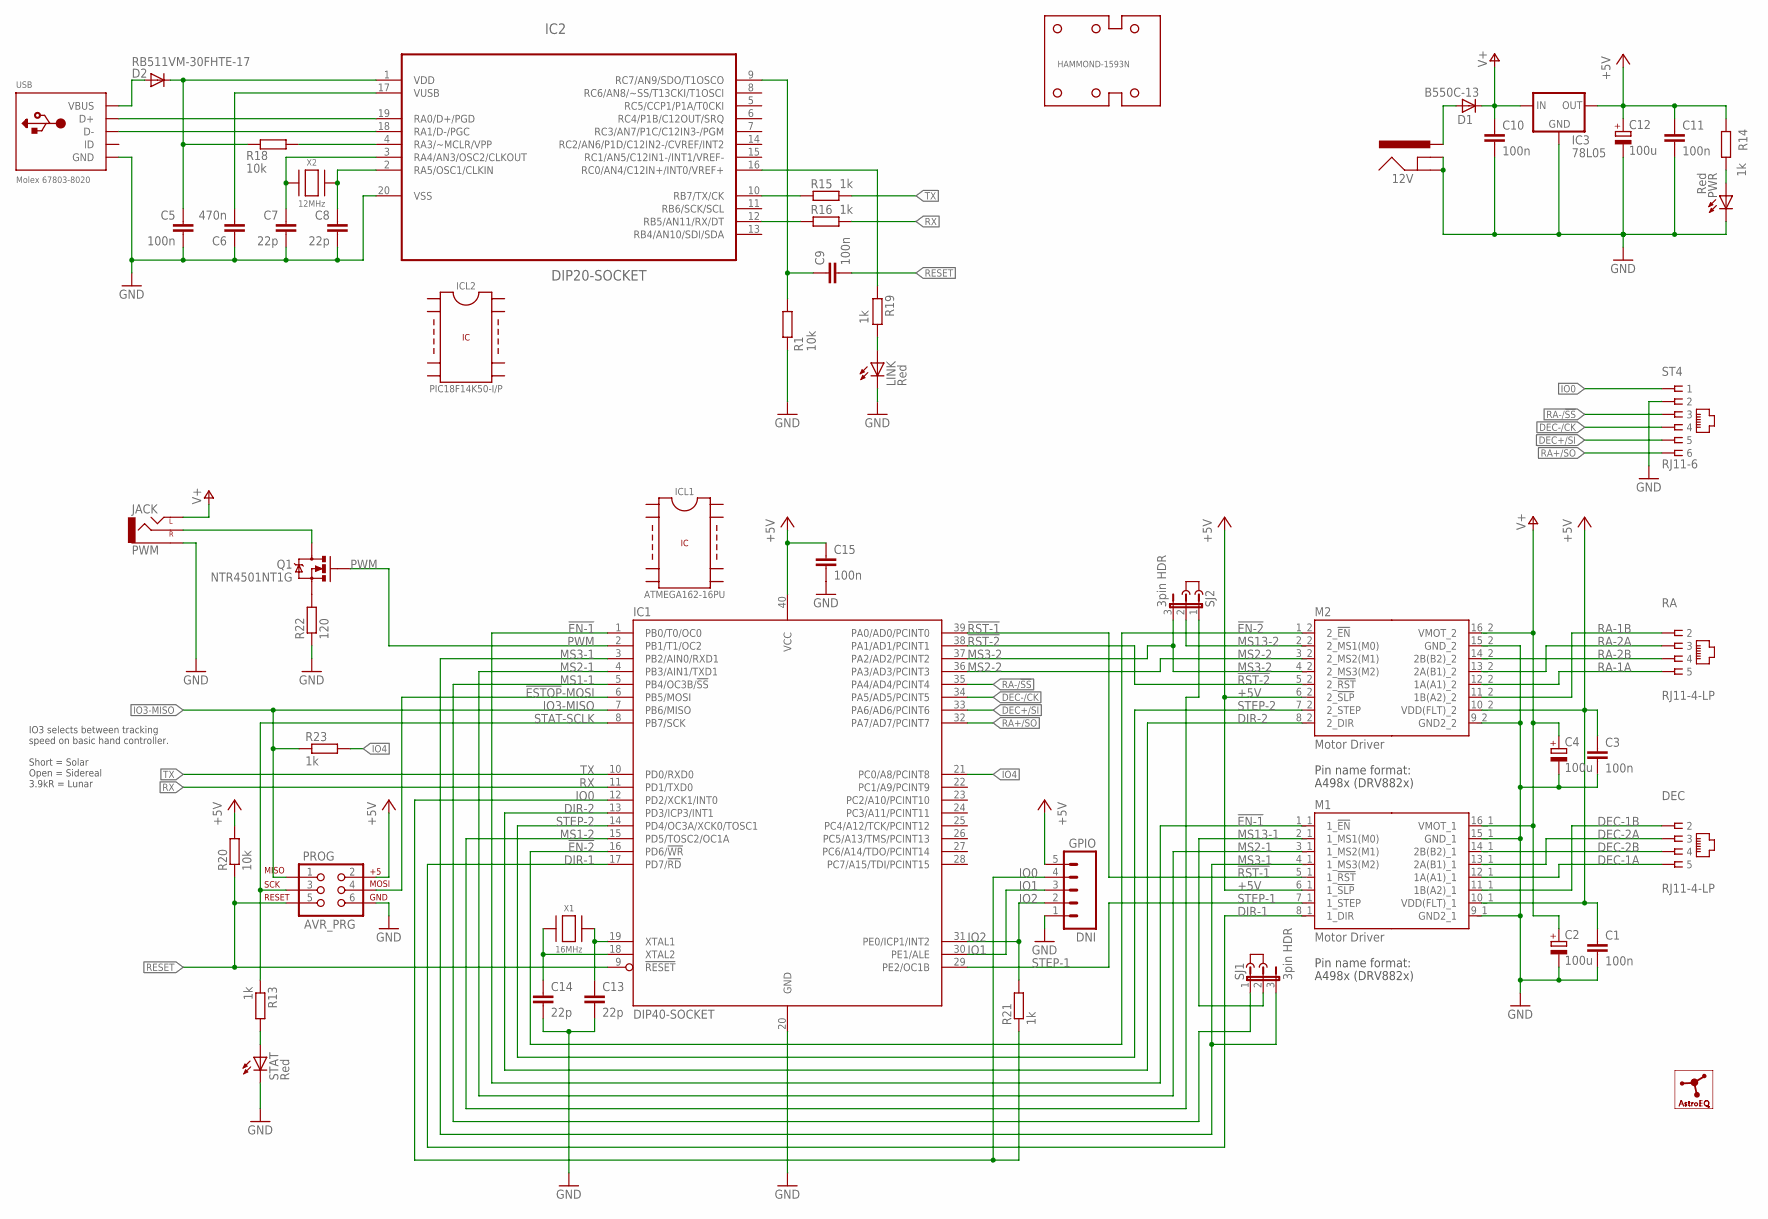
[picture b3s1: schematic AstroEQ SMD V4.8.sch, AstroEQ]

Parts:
12V: POWER_JACKPTH; POWER_JACK_PTH; MPN MJ-179PH
C1, C3, C5, C9, C10, C11, C15: 100n; C0603; MPN MC0603F104Z250CT
C2, C4, C12: 100u; PANASONIC_D; MPN 865080545012
C6: 470n; C0603; MPN MC0603F474Z160CT
C7, C8, C13, C14: 22p; C0603; MPN MC0603N220J500CT
D1: B550C-13; SMC; MPN B550C-13-F
D2: RB511VM-30FHTE-17; SOD-323; MPN RB511VM-30FHTE-17
DEC: RJ11-4-LP; RJ11-NO_SHIELD-4-LP; MPN 95501-2641
GPIO: DNI; 1X05
HAMMOND-1593N: HAMMOND-1593N-4HOLE; HAMMOND-1593N4HOLES; MPN 1593NBK
IC1: DIP40-SOCKET; DIL40; MPN 2227MC-40-06-05-F1
IC2: DIP20-SOCKET; DIL20-SKT
IC3: 78L05; SOT89; MPN L78L05ACUTR
ICL1: ATMEGA162-16PU; IC; MPN ATMEGA162-16PU
ICL2: PIC18F14K50-I/P; IC; MPN PIC18F14K50-I/P
J2, J3: DNI; JUMP; MPN 969102-0000-DA
LINK: Red; SML1206-SIDE; MPN 155124RS73200
LOGO1: DNI; ASTROEQ-SMALL
M1: Motor Driver; CARRIER-HV-DUAL; MPN CES-116-01-T-S
M2: Motor Driver; CARRIER-LV-DUAL; MPN CES-116-01-T-S
PROG: AVR_PRG; 2X3; MPN M20-9980346
PWM: JACK; AUDIO-JACK; MPN FC68131
PWR: Red; SML1206-SIDE; MPN 155124RS73200
Q1: NTR4501NT1G; SOT23-3; MPN NTR4501NT1G
R1, R18, R20: 10k; R0603; MPN MCWR06X1002FTL
R13, R14, R15, R16, R19, R21, R23: 1k; R0603; MPN MCWR06X1001FTL
R22: 120; R0805; MPN MCWR08X1200FTL
RA: RJ11-4-LP; RJ11-NO_SHIELD-4-LP; MPN 95501-2641
SJ1, SJ2: 3pin HDR; JP2; MPN M20-9990345.
ST4: RJ11-6; RJ11-NO_SHIELD-LP; MPN 95501-2661
STAT: Red; SML1206-SIDE; MPN 155124RS73200
USB: Molex 67803-8020; USB-MINIAB; MPN 67803-8020
X1: 16MHz; NX5032; MPN 7A-16.000MAAJ-T
X2: 12MHz; NX5032; MPN 7A-12.000MAAJ-T

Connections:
!EN-1: IC1.1 (PB0/T0/OC0), M2.1_1 (1_!EN)
!EN-2: IC1.16 (PD6/!WR), M2.1_2 (2_!EN)
!ESTOP!-MOSI: IC1.6 (PB5/MOSI), PROG.4
!RST-1: IC1.39 (PA0/AD0/PCINT0), M2.5_1 (1_!RST)
!RST-2: IC1.38 (PA1/AD1/PCINT1), M2.5_2 (2_!RST)
+5V: C1.1, C3.1, C11.1, C12.+, C15.1, GPIO.5, IC1.40 (VCC), IC3.1 (OUT), M1.10_1 (VDD(FLT)_1), M1.10_2 (VDD(FLT)_2), M2.6_1 (1_!SLP), M2.6_2 (2_!SLP), PROG.2, R14.1, R20.2
AVROSC1: C13.1, IC1.19 (XTAL1), X1.P$2
AVROSC2: C14.1, IC1.18 (XTAL2), X1.P$1
DEC+/SI: IC1.33 (PA6/AD6/PCINT6), ST4.5
DEC-1A: DEC.5, M1.12_1 (1A(A1)_1)
DEC-1B: DEC.2, M1.11_1 (1B(A2)_1)
DEC-2A: DEC.3, M1.13_1 (2A(B1)_1)
DEC-2B: DEC.4, M1.14_1 (2B(B2)_1)
DEC-/CK: IC1.34 (PA5/AD5/PCINT5), ST4.4
DIR-1: IC1.17 (PD7/!RD), M2.8_1 (1_DIR)
DIR-2: IC1.13 (PD3/ICP3/INT1), M2.8_2 (2_DIR)
DTR: C9.1, IC2.9 (RC7/AN9/SDO/T1OSCO), R1.1
D_N: IC2.18 (RA1/D-/PGC), USB.D-
D_P: IC2.19 (RA0/D+/PGD), USB.D+
GND: 12V.GND, 12V.GNDBREAK, C1.2, C2.-, C3.2, C4.-, C5.2, C6.1, C7.2, C8.2, C10.2, C11.2, C12.-, C13.2, C14.2, C15.2, GPIO.1, IC1.20 (GND), IC2.20 (VSS), IC3.2 (GND), IC3.4 (GND), LINK.C, LINK.E (C), M1.9_1 (GND2_1), M1.9_2 (GND2_2), M1.15_1 (GND_1), M1.15_2 (GND_2), PROG.6, PWM.SLEEVE, PWR.C, PWR.E (C), R1.2, R22.1, ST4.2, STAT.C, STAT.E (C), USB.GND, USB.GND1 (GND), USB.GND2 (GND), USB.GND3 (GND), USB.GND4 (GND)
IO0: GPIO.4, IC1.12 (PD2/XCK1/INT0), R21.1, ST4.1
IO1: GPIO.3, IC1.30 (PE1/ALE)
IO2: GPIO.2, IC1.31 (PE0/ICP1/INT2), R21.2
IO3-MISO: IC1.7 (PB6/MISO), PROG.1, R23.1
IO4: IC1.21 (PC0/A8/PCINT8), R23.2
MCLR: IC2.4 (RA3/~MCLR/VPP), R18.1
MS1-1: IC1.5 (PB4/OC3B/!SS), SJ1.1
MS1-2: IC1.15 (PD5/TOSC2/OC1A), SJ2.1
MS2-1: IC1.4 (PB3/AIN1/TXD1), M2.3_1 (1_MS2(M1))
MS2-2: IC1.36 (PA3/AD3/PCINT3), M2.3_2 (2_MS2(M1))
MS3-1: IC1.3 (PB2/AIN0/RXD1), M2.4_1 (1_MS3(M2)), SJ1.3
MS3-2: IC1.37 (PA2/AD2/PCINT2), M2.4_2 (2_MS3(M2)), SJ2.3
MS13-1: M2.2_1 (1_MS1(M0)), SJ1.2
MS13-2: M2.2_2 (2_MS1(M0)), SJ2.2
PWM: IC1.2 (PB1/T1/OC2), Q1.1 (G)
PWM-ILIM: Q1.2 (S), R22.2
PWM-OD: PWM.RING (RIGHT), Q1.3 (D)
PWRLED: PWR.A, R14.2
RA+/SO: IC1.32 (PA7/AD7/PCINT7), ST4.6
RA-1A: M1.12_2 (1A(A1)_2), RA.5
RA-1B: M1.11_2 (1B(A2)_2), RA.2
RA-2A: M1.13_2 (2A(B1)_2), RA.3
RA-2B: M1.14_2 (2B(B2)_2), RA.4
RA-/!SS: IC1.35 (PA4/AD4/PCINT4), ST4.3
RESET: C9.2, IC1.9 (!RESET), PROG.5, R20.1
RX: IC1.11 (PD1/TXD0), R16.1
RX(USB): IC2.12 (RB5/AN11/RX/DT), R16.2
STAT-SCLK: IC1.8 (PB7/SCK), PROG.3, R13.1
STATLED: R13.2, STAT.A
STEP-1: IC1.29 (PE2/OC1B), M2.7_1 (1_STEP)
STEP-2: IC1.14 (PD4/OC3A/XCK0/TOSC1), M2.7_2 (2_STEP)
TX: IC1.10 (PD0/RXD0), R15.1
TX(USB): IC2.10 (RB7/TX/CK), R15.2
USBLED: LINK.A, R19.1
USBOSC1: C8.1, IC2.2 (RA5/OSC1/CLKIN), X2.P$2
USBOSC2: C7.1, IC2.3 (RA4/AN3/OSC2/CLKOUT), X2.P$1
USBSTAT: IC2.16 (RC0/AN4/C12IN+/INT0/VREF+), R19.2
V+: C2.+, C4.+, C10.1, D1.C, IC3.3 (IN), M1.16_1 (VMOT_1), M1.16_2 (VMOT_2), PWM.TIP (LEFT)
VBUS: D2.2 (A), USB.VBUS
VIN: 12V.PWR, D1.A
VPIC: C5.1, D2.1 (C), IC2.1 (VDD), R18.2
VUSB: C6.2, IC2.17 (VUSB)

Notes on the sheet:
IO3 selects between tracking speed on basic hand controller. Short = Solar Open = Sidereal 3.9kR = Lunar

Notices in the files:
AstroEQ-Hardware/ARD/AstroEQ Arduino Mega.brd:
(C) 2017-2026
AstroEQ-Hardware/EQ5/AstroEQ SMD V4.8 (EQ5).brd:
(C) 2013-26
AstroEQ-Hardware/PTH/AstroEQ PTH V4.8.brd:
(C) 2012-26
parts and their libraries:
SparkFun: Licensing: CC v3.0 Share-Alike You are welcome to use this library for commercial purposes.
